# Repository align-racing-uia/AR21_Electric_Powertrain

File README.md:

<h1 align="center"> Align Racing 2021 - Electric Powertrain </h1> <br>
<p align="center">
    
</p>

<!-- START doctoc generate TOC please keep comment here to allow auto update -->
<!-- DON'T EDIT THIS SECTION, INSTEAD RE-RUN doctoc TO UPDATE -->
## Table of contents

- [Introduction](#introduction)
- [Align Racing UiA](#alignracinguia)
- [Rules for file structure](#rulesforfilestructure)
- [License](#license)

<!-- END doctoc generated TOC please keep comment here to allow auto update -->

## Introduction

This is the repository for Align Racing's formula student race Electric Powertrain

## Align Racing UiA

<a href="http://www.alignracing.no/">Align Racing UiA (AR)</a> is a multidisciplinary student organisation at <a href="https://www.uia.no/">The University of Agder (UiA)</a>, that take part in the world’s largest yearly engineering competition; <a href="https://www.imeche.org/events/formula-student">Formula Student (FS)</a>. The organisation continuously consists of around 60 students, from a wide variety of disciplines. The competition includes developing, building, budgeting and marketing a small scale formula type racing car. AR takes this a bit further by having more focus on developing a strong organisation, open for all disciplines, that gives the members a taste of future work-life.

## Rules for directory structure
<h4>General directory structure:</h4>

* AR”YEAR”
    * AR”YEAR”_“PROJECT”
        - AR”YEAR”_“SUBPROJECT”
            - “PROJECT”_code
            - “PROJECT”_datasheets
            - “PROJECT”_images
            - “PROJECT”_schematic
            - “PROJECT”_simulink

<h4>Directory structure example:</h4>

* AR19
    * AR19_ETC
        - AR19_ETC_ACM_ETB
            - ACM_ETB_code
            - ACM_ETB_datasheets
            - ACM_ETB_images
            - ACM_ETB_schematic
            - ACM_ETB_simulink

## License
All content included in this Git repository is under the license:

Creative Commons Attribution-NonCommercial-ShareAlike 4.0 International

You are free to:
* <b> Share </b> — copy and redistribute the material in any medium or format
* <b> Adapt </b> — remix, transform, and build upon the material

Under the following terms:
* <b> Attribution </b> — You must give appropriate credit, provide a link to the license, and indicate if changes were made. You may do so in any reasonable manner, but not in any way that suggests the licensor endorses you or your use.
* <b> NonCommercial </b> — You may not use the material for commercial purposes.
* <b> ShareAlike </b> — If you remix, transform, or build upon the material, you must distribute your contributions under the same license as the original.
* <b> No additional restrictions </b> — You may not apply legal terms or technological measures that legally restrict others from doing anything the license permits.

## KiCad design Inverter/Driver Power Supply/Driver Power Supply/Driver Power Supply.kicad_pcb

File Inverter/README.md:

## Inverter

This is the folder for Inverter Design.

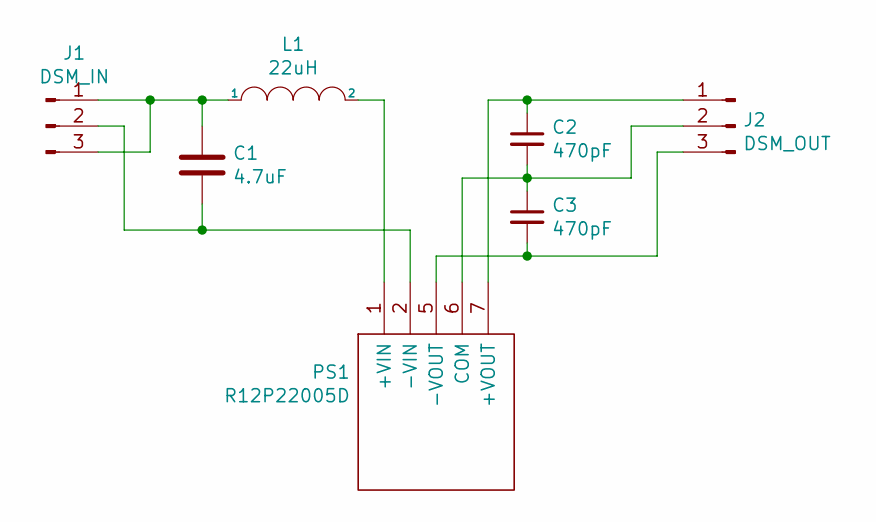
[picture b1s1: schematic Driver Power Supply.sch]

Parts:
C1: 4.7uF; C_0805_2012Metric
C2, C3: 470pF; C_0603_1608Metric
J1: DSM_IN; PinHeader_1x03_P2.00mm_Vertical
J2: DSM_OUT; PinHeader_1x03_P2.00mm_Vertical
L1: 22uH; L_1812_4532Metric
PS1: R12P22005D; R15P21503D; Manufacturer_Part_Number R12P22005D; Mouser Part Number 919-R12P22005D

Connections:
unnamed: C1.1, J1.1, J1.3, L1.1
unnamed: C1.2, J1.2, PS1.2 (-VIN)
unnamed: C2.1, J2.1, PS1.7 (+VOUT)
unnamed: C2.2, C3.1, J2.2, PS1.6 (COM)
unnamed: C3.2, J2.3, PS1.5 (-VOUT)
unnamed: L1.2, PS1.1 (+VIN)

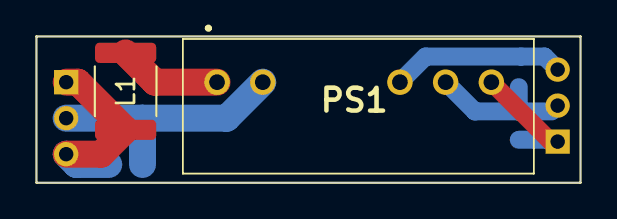
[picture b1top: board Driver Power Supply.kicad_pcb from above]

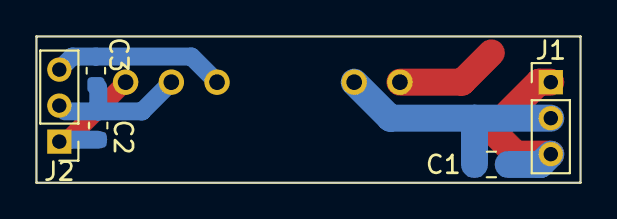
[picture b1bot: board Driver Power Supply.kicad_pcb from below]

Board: 2 copper layers, 30.2 x 8.1 mm, 7 parts (5 on the bottom side), 6 nets.

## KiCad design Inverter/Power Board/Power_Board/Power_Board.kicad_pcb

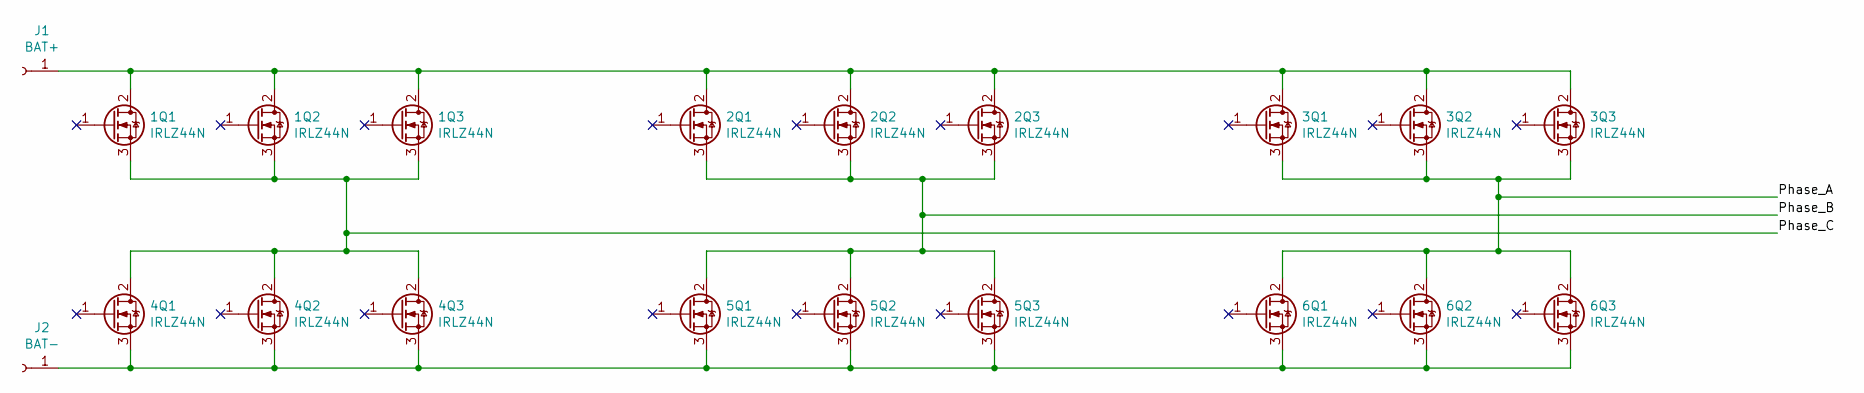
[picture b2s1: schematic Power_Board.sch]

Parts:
1Q1, 1Q2, 1Q3, 2Q1, 2Q2, 2Q3, 3Q1, 3Q2, 3Q3, 4Q1, 4Q2, 4Q3, 5Q1, 5Q2, 5Q3, 6Q1, 6Q2, 6Q3: IRLZ44N; TO-247-3_Horizontal_TabUp
J1: BAT+; MountingHole_8.4mm_M8_Pad
J2: BAT-; MountingHole_8.4mm_M8_Pad

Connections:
/Phase_A: 3Q1.3 (S), 3Q2.3 (S), 3Q3.3 (S), 6Q1.2 (D), 6Q2.2 (D), 6Q3.2 (D)
/Phase_B: 2Q1.3 (S), 2Q2.3 (S), 2Q3.3 (S), 5Q1.2 (D), 5Q2.2 (D), 5Q3.2 (D)
/Phase_C: 1Q1.3 (S), 1Q2.3 (S), 1Q3.3 (S), 4Q1.2 (D), 4Q2.2 (D), 4Q3.2 (D)
unnamed: 1Q1.2 (D), 1Q2.2 (D), 1Q3.2 (D), 2Q1.2 (D), 2Q2.2 (D), 2Q3.2 (D), 3Q1.2 (D), 3Q2.2 (D), 3Q3.2 (D), J1.1
unnamed: 4Q1.3 (S), 4Q2.3 (S), 4Q3.3 (S), 5Q1.3 (S), 5Q2.3 (S), 5Q3.3 (S), 6Q1.3 (S), 6Q2.3 (S), 6Q3.3 (S), J2.1

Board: 2 copper layers, 20 parts (0 on the bottom side), 5 nets, no tracks yet.

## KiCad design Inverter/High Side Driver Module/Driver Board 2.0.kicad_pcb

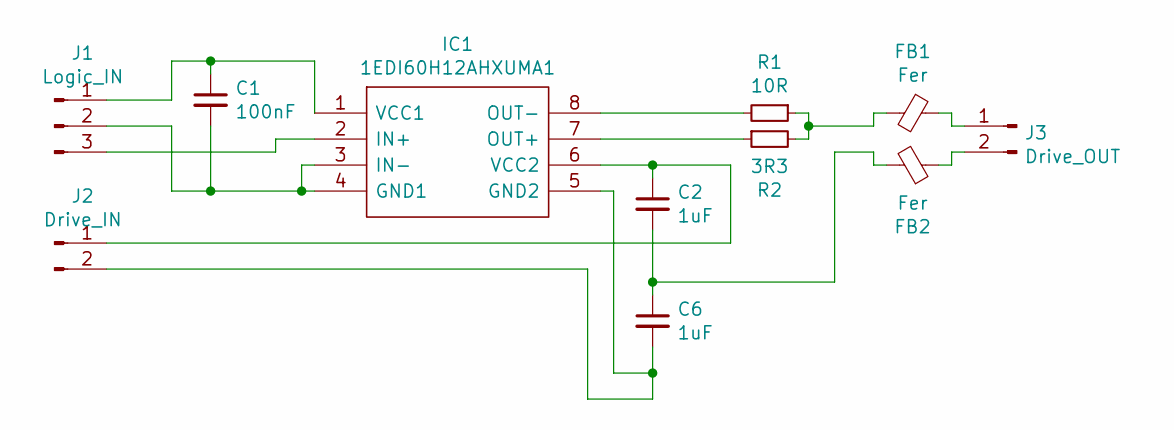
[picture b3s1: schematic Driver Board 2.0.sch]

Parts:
C1: 100nF; C_0603_1608Metric_Pad1.05x0.95mm_HandSolder
C2, C6: 1uF; C_0603_1608Metric_Pad1.05x0.95mm_HandSolder
FB1, FB2: Fer; R_0603_1608Metric
IC1: 1EDI60H12AHXUMA1; SOIC127P1030X265-8N; Manufacturer_Part_Number 1EDI60H12AHXUMA1; Mouser Part Number 726-1EDI60H12AHXUMA1
J1: Logic_IN; PinHeader_1x03_P2.00mm_Vertical
J2: Drive_IN; PinHeader_1x02_P2.00mm_Vertical
J3: Drive_OUT; PinHeader_1x02_P2.54mm_Vertical
R1: 10R; R_0603_1608Metric
R2: 3R3; R_0603_1608Metric

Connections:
unnamed: C1.1, IC1.1 (VCC1), J1.1
unnamed: C1.2, IC1.3 (IN-), IC1.4 (GND1), J1.2
unnamed: C2.1, IC1.6 (VCC2), J2.1
unnamed: C2.2, C6.1, FB2.2
unnamed: C6.2, IC1.5 (GND2), J2.2
unnamed: FB1.1, J3.1
unnamed: FB1.2, R1.1, R2.2
unnamed: FB2.1, J3.2
unnamed: IC1.2 (IN+), J1.3
unnamed: IC1.7 (OUT+), R2.1
unnamed: IC1.8 (OUT-), R1.2

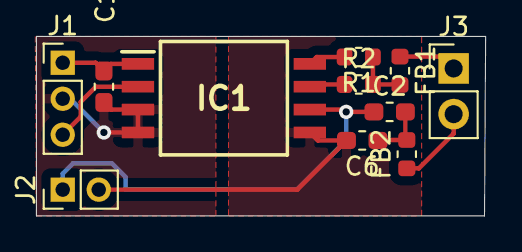
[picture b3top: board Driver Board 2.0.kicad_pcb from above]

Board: 2 copper layers, 25.0 x 10.0 mm, 11 parts (0 on the bottom side), 11 nets.

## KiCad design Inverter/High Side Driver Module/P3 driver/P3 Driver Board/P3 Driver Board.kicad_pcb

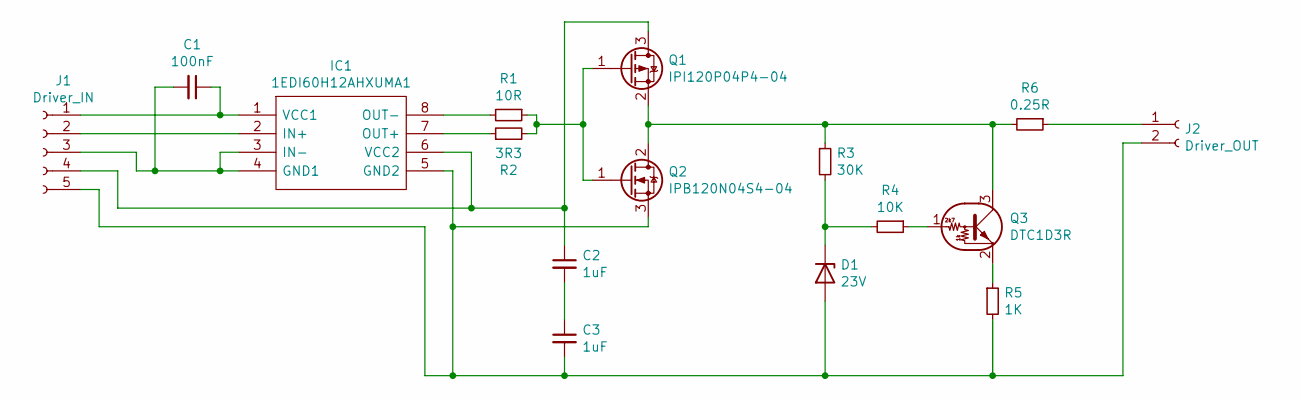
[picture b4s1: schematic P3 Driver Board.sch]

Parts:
C1: 100nF; R_0603_1608Metric
C2, C3: 1uF; R_0603_1608Metric
D1: 23V; R_0603_1608Metric
IC1: 1EDI60H12AHXUMA1; SOIC127P1030X265-8N; Manufacturer_Part_Number 1EDI60H12AHXUMA1; Mouser Part Number 726-1EDI60H12AHXUMA1
J1: Driver_IN; PinHeader_1x05_P2.54mm_Vertical
J2: Driver_OUT; PinHeader_1x02_P2.54mm_Vertical
Q1: IPI120P04P4-04; TO-263-2
Q2: IPB120N04S4-04; TO-263-2
Q3: DTC1D3R; SOT-23
R1: 10R; R_0603_1608Metric
R2: 3R3; R_0603_1608Metric
R3: 30K; R_0603_1608Metric
R4: 10K; R_0603_1608Metric
R5: 1K; R_0603_1608Metric
R6: 0.25R; R_4020_10251Metric

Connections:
unnamed: C1.1, IC1.1 (VCC1), J1.1
unnamed: C1.2, IC1.3 (IN-), IC1.4 (GND1), J1.3
unnamed: C2.1, IC1.6 (VCC2), J1.4, Q1.3 (D)
unnamed: C2.2, C3.1
unnamed: C3.2, D1.2 (A), IC1.5 (GND2), J1.5, J2.2, Q2.3 (S), R5.2
unnamed: D1.1 (K), R3.2, R4.2
unnamed: IC1.2 (IN+), J1.2
unnamed: IC1.7 (OUT+), R2.1
unnamed: IC1.8 (OUT-), R1.2
unnamed: J2.1, R6.1
unnamed: Q1.1 (G), Q2.1 (G), R1.1, R2.2
unnamed: Q1.2 (S), Q2.2 (D), Q3.3 (C), R3.1, R6.2
unnamed: Q3.1 (B), R4.1
unnamed: Q3.2 (E), R5.1

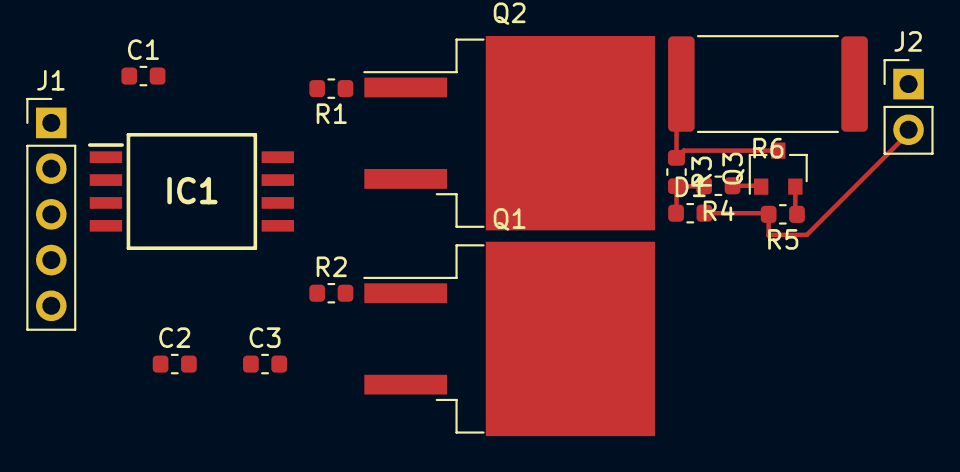
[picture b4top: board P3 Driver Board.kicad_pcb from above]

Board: 2 copper layers, 16 parts (0 on the bottom side), 14 nets.

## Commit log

2020-09-27 Updated Readme.md with Electric powertrain
2020-09-27 Initialized inverter folder
2020-09-27 Initial upload
2021-02-03 Drawing for PCB design of temp sensors on module.
